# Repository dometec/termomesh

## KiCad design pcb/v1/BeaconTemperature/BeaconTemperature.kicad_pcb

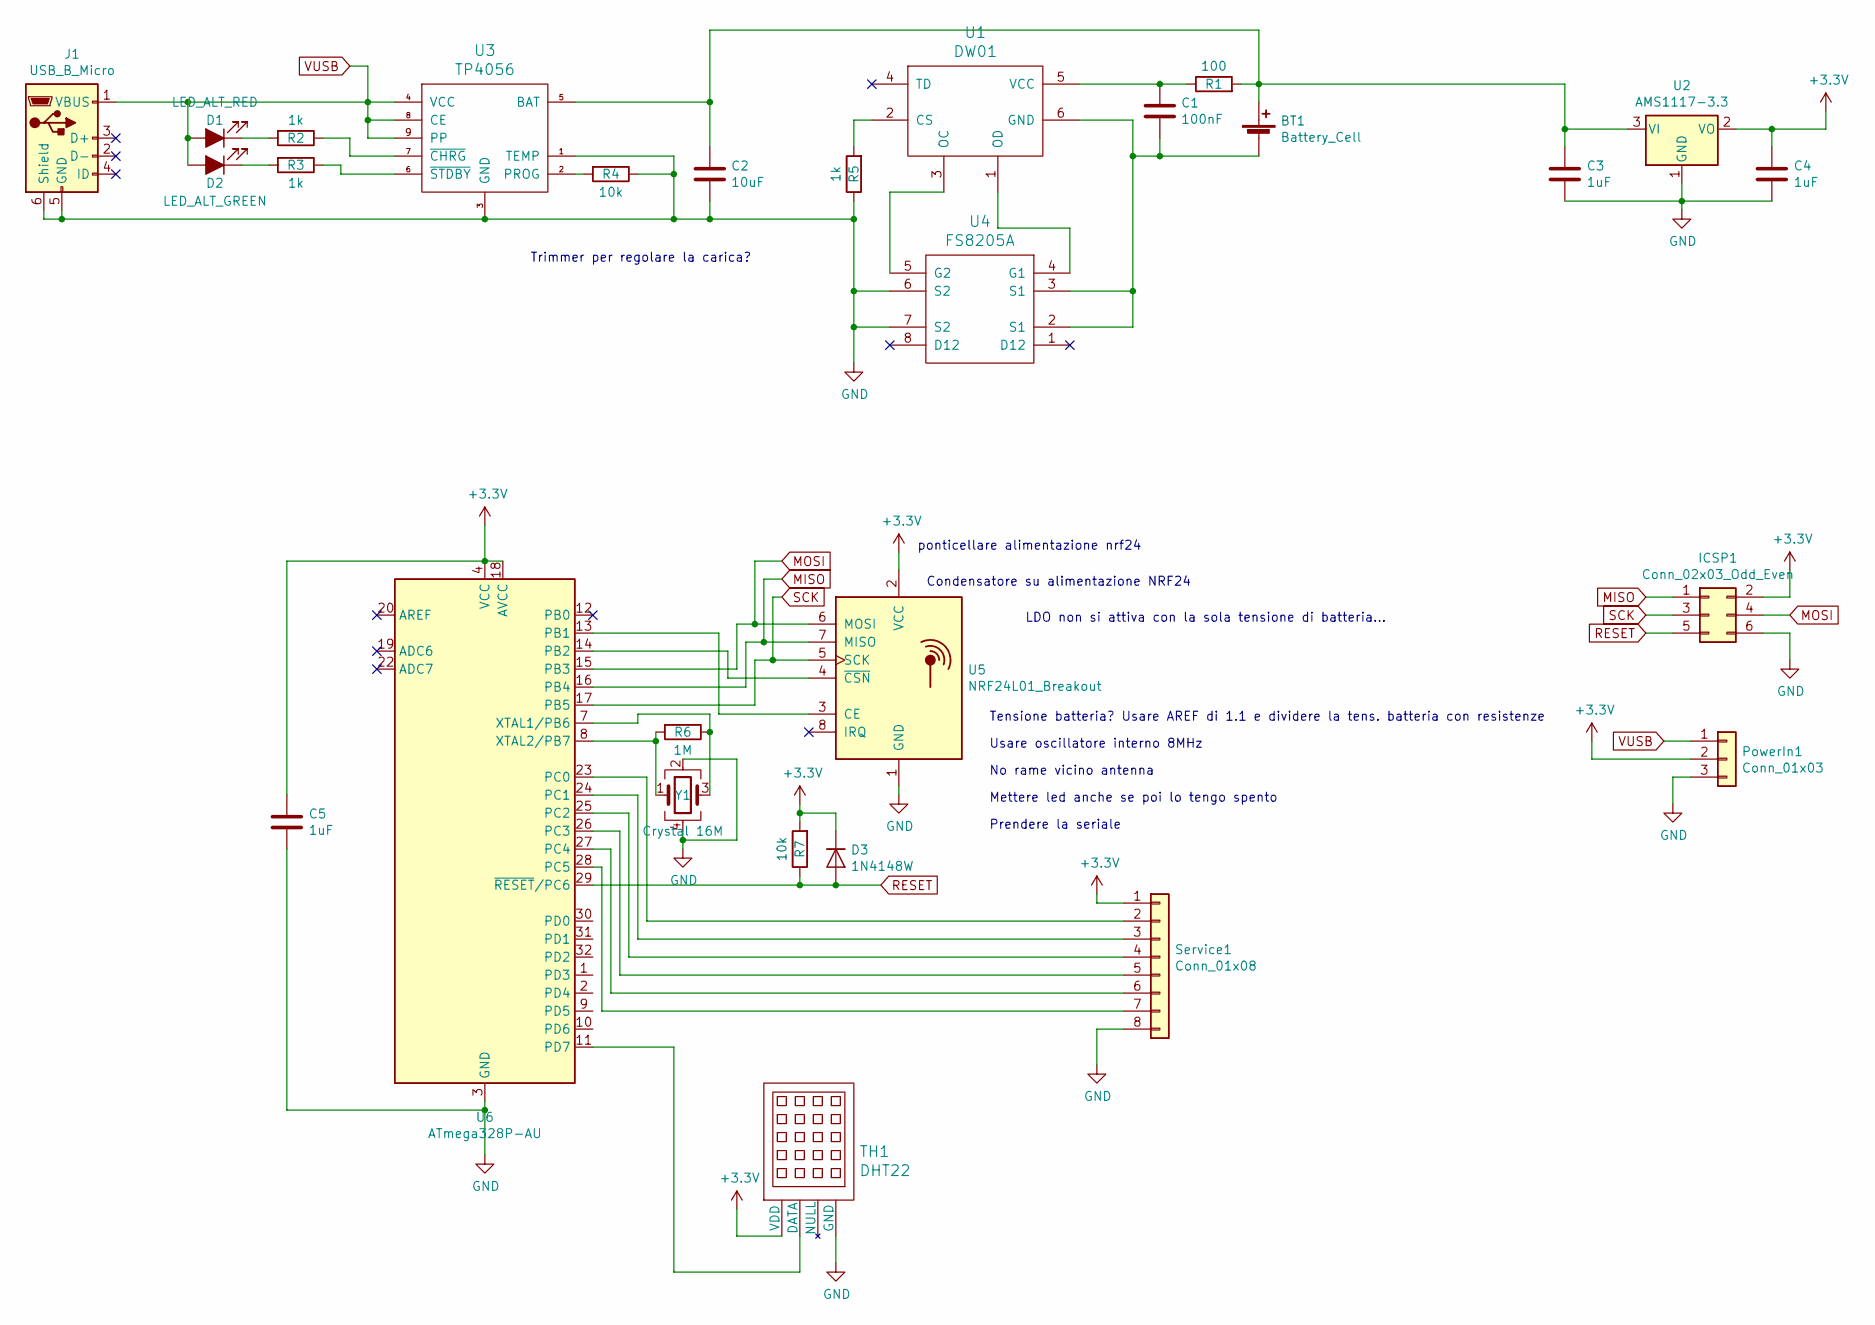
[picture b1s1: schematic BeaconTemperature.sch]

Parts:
BT1: Battery_Cell; BatteryHolder_MPD_BH-18650-PC2
C1: 100nF; C_0603_1608Metric; LCSC C14663
C2: 10uF; C_0603_1608Metric; LCSC C19702
C3, C4: 1uF; C_0603_1608Metric; LCSC C1525
C5: 1uF; C_0805_2012Metric; LCSC C28323
D1: LED_ALT_RED; LED_0603_1608Metric; LCSC C2286
D2: LED_ALT_GREEN; LED_0603_1608Metric; LCSC C72043
D3: 1N4148W; D_SOD-323F; LCSC C2128
ICSP1: Conn_02x03_Odd_Even; PinHeader_2x03_P2.54mm_Vertical
J1: USB_B_Micro; USB_Micro-B_Molex_47346-0001
PowerIn1: Conn_01x03; PinHeader_1x03_P2.54mm_Vertical
R1: 100; R_0603_1608Metric; LCSC C22775
R2, R3, R5: 1k; R_0603_1608Metric; LCSC C21190
R4, R7: 10k; R_0603_1608Metric; LCSC C25804
R6: 1M; R_0603_1608Metric; LCSC C22935
Service1: Conn_01x08; PinHeader_1x08_P2.54mm_Vertical
TH1: DHT22; DHT22_Temperature_Humidity
U1: DW01; SOT-23-6; LCSC C14213
U2: AMS1117-3.3; SOT-223-3_TabPin2; LCSC C6186
U3: TP4056; TP4056_SOP-8-PP; LCSC C16581
U4: FS8205A; TSSOP-8_4.4x3mm_P0.65mm; LCSC C16052
U5: NRF24L01_Breakout; NRF24L01-SMD
U6: ATmega328P-AU; TQFP-32_7x7mm_P0.8mm; LCSC C14877
Y1: Crystal 16M; Oscillator_SMD_EuroQuartz_XO32-4Pin_3.2x2.5mm; LCSC C13738

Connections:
+3V3: C4.1, C5.1, D3.1 (K), ICSP1.2, PowerIn1.2, R7.2, Service1.1, TH1.1 (VDD), U2.2 (VO), U5.2 (VCC), U6.4 (VCC), U6.6 (VCC), U6.18 (AVCC)
GND: C2.2, C3.2, C4.2, C5.2, ICSP1.6, J1.5 (GND), J1.6 (Shield), PowerIn1.3, R4.1, R5.1, Service1.8, TH1.4 (GND), U2.1 (GND), U3.1 (TEMP), U3.3 (GND), U4.6 (S2), U4.7 (S2), U5.1 (GND), U6.3 (GND), U6.5 (GND), U6.21 (GND), Y1.2, Y1.4
MISO: ICSP1.1, U5.7 (MISO), U6.16 (PB4)
MOSI: ICSP1.4, U5.6 (MOSI), U6.15 (PB3)
unnamed: BT1.1 (+), C2.1, C3.1, R1.2, U2.3 (VI), U3.5 (BAT)
unnamed: BT1.2 (-), C1.2, U1.6 (GND), U4.2 (S1), U4.3 (S1)
unnamed: C1.1, R1.1, U1.5 (VCC)
unnamed: D1.1 (K), R2.2
unnamed: D2.1 (K), R3.2
unnamed: R2.1, U3.7 (~CHRG)
unnamed: R3.1, U3.6 (~STDBY)
unnamed: R4.2, U3.2 (PROG)
unnamed: R5.2, U1.2 (CS)
unnamed: R6.1, U6.7 (XTAL1/PB6), Y1.3
unnamed: R6.2, U6.8 (XTAL2/PB7), Y1.1
unnamed: Service1.2, U6.23 (PC0)
unnamed: Service1.3, U6.24 (PC1)
unnamed: Service1.4, U6.25 (PC2)
unnamed: Service1.5, U6.26 (PC3)
unnamed: Service1.6, U6.27 (PC4)
unnamed: Service1.7, U6.28 (PC5)
unnamed: TH1.2 (DATA), U6.11 (PD7)
unnamed: U1.1 (OD), U4.4 (G1)
unnamed: U1.3 (OC), U4.5 (G2)
unnamed: U5.3 (CE), U6.13 (PB1)
unnamed: U5.4 (~CSN), U6.14 (PB2)
RESET: D3.2 (A), ICSP1.5, R7.1, U6.29 (~RESET~/PC6)
SCK: ICSP1.3, U5.5 (SCK), U6.17 (PB5)
VUSB: D1.2 (A), D2.2 (A), J1.1 (VBUS), PowerIn1.1, U3.4 (VCC), U3.8 (CE), U3.9 (PP)

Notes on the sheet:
Prendere la seriale
Mettere led anche se poi lo tengo spento
No rame vicino antenna
Usare oscillatore interno 8MHz
ponticellare alimentazione nrf24
Tensione batteria? Usare AREF di 1.1 e dividere la tens. batteria con resistenze
Trimmer per regolare la carica?
LDO non si attiva con la sola tensione di batteria...
Condensatore su alimentazione NRF24

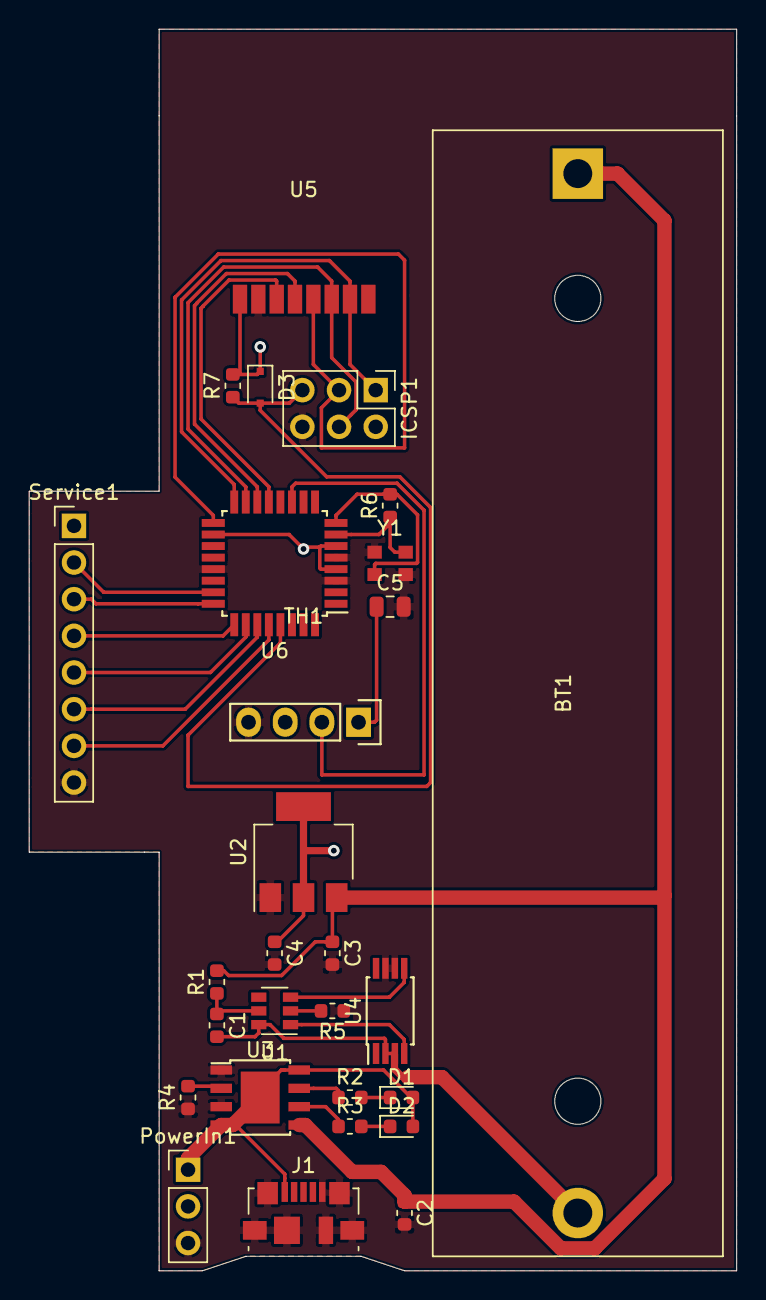
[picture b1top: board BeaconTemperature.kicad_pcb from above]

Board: 2 copper layers, 49.0 x 86.0 mm, 28 parts (0 on the bottom side), 29 nets.

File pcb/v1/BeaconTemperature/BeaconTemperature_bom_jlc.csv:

"Comment","Designator","Footprint","LCSC Part #"
"100nF","C1","C_0603_1608Metric","C14663"
"10uF","C2","C_0603_1608Metric","C19702"
"1uF","C4,C3","C_0603_1608Metric","C1525"
"1uF","C5","C_0805_2012Metric","C28323"
"LED_ALT_RED","D1","LED_0603_1608Metric","C2286"
"LED_ALT_GREEN","D2","LED_0603_1608Metric","C72043"
"1N4148W","D3","D_SOD-323F","C2128"
"100","R1","R_0603_1608Metric","C22775"
"1k","R2,R3,R5","R_0603_1608Metric","C21190"
"10k","R4,R7","R_0603_1608Metric","C25804"
"1M","R6","R_0603_1608Metric","C22935"
"DW01","U1","SOT-23-6","C14213"
"AMS1117-3.3","U2","SOT-223-3_TabPin2","C6186"
"TP4056","U3","TP4056_SOP-8-PP","C16581"
"FS8205A","U4","TSSOP-8_4.4x3mm_P0.65mm","C16052"
"ATmega328P-AU","U6","TQFP-32_7x7mm_P0.8mm","C14877"
"Crystal 16M","Y1","Oscillator_SMD_EuroQuartz_XO32-4Pin_3.2x2.5mm","C13738"

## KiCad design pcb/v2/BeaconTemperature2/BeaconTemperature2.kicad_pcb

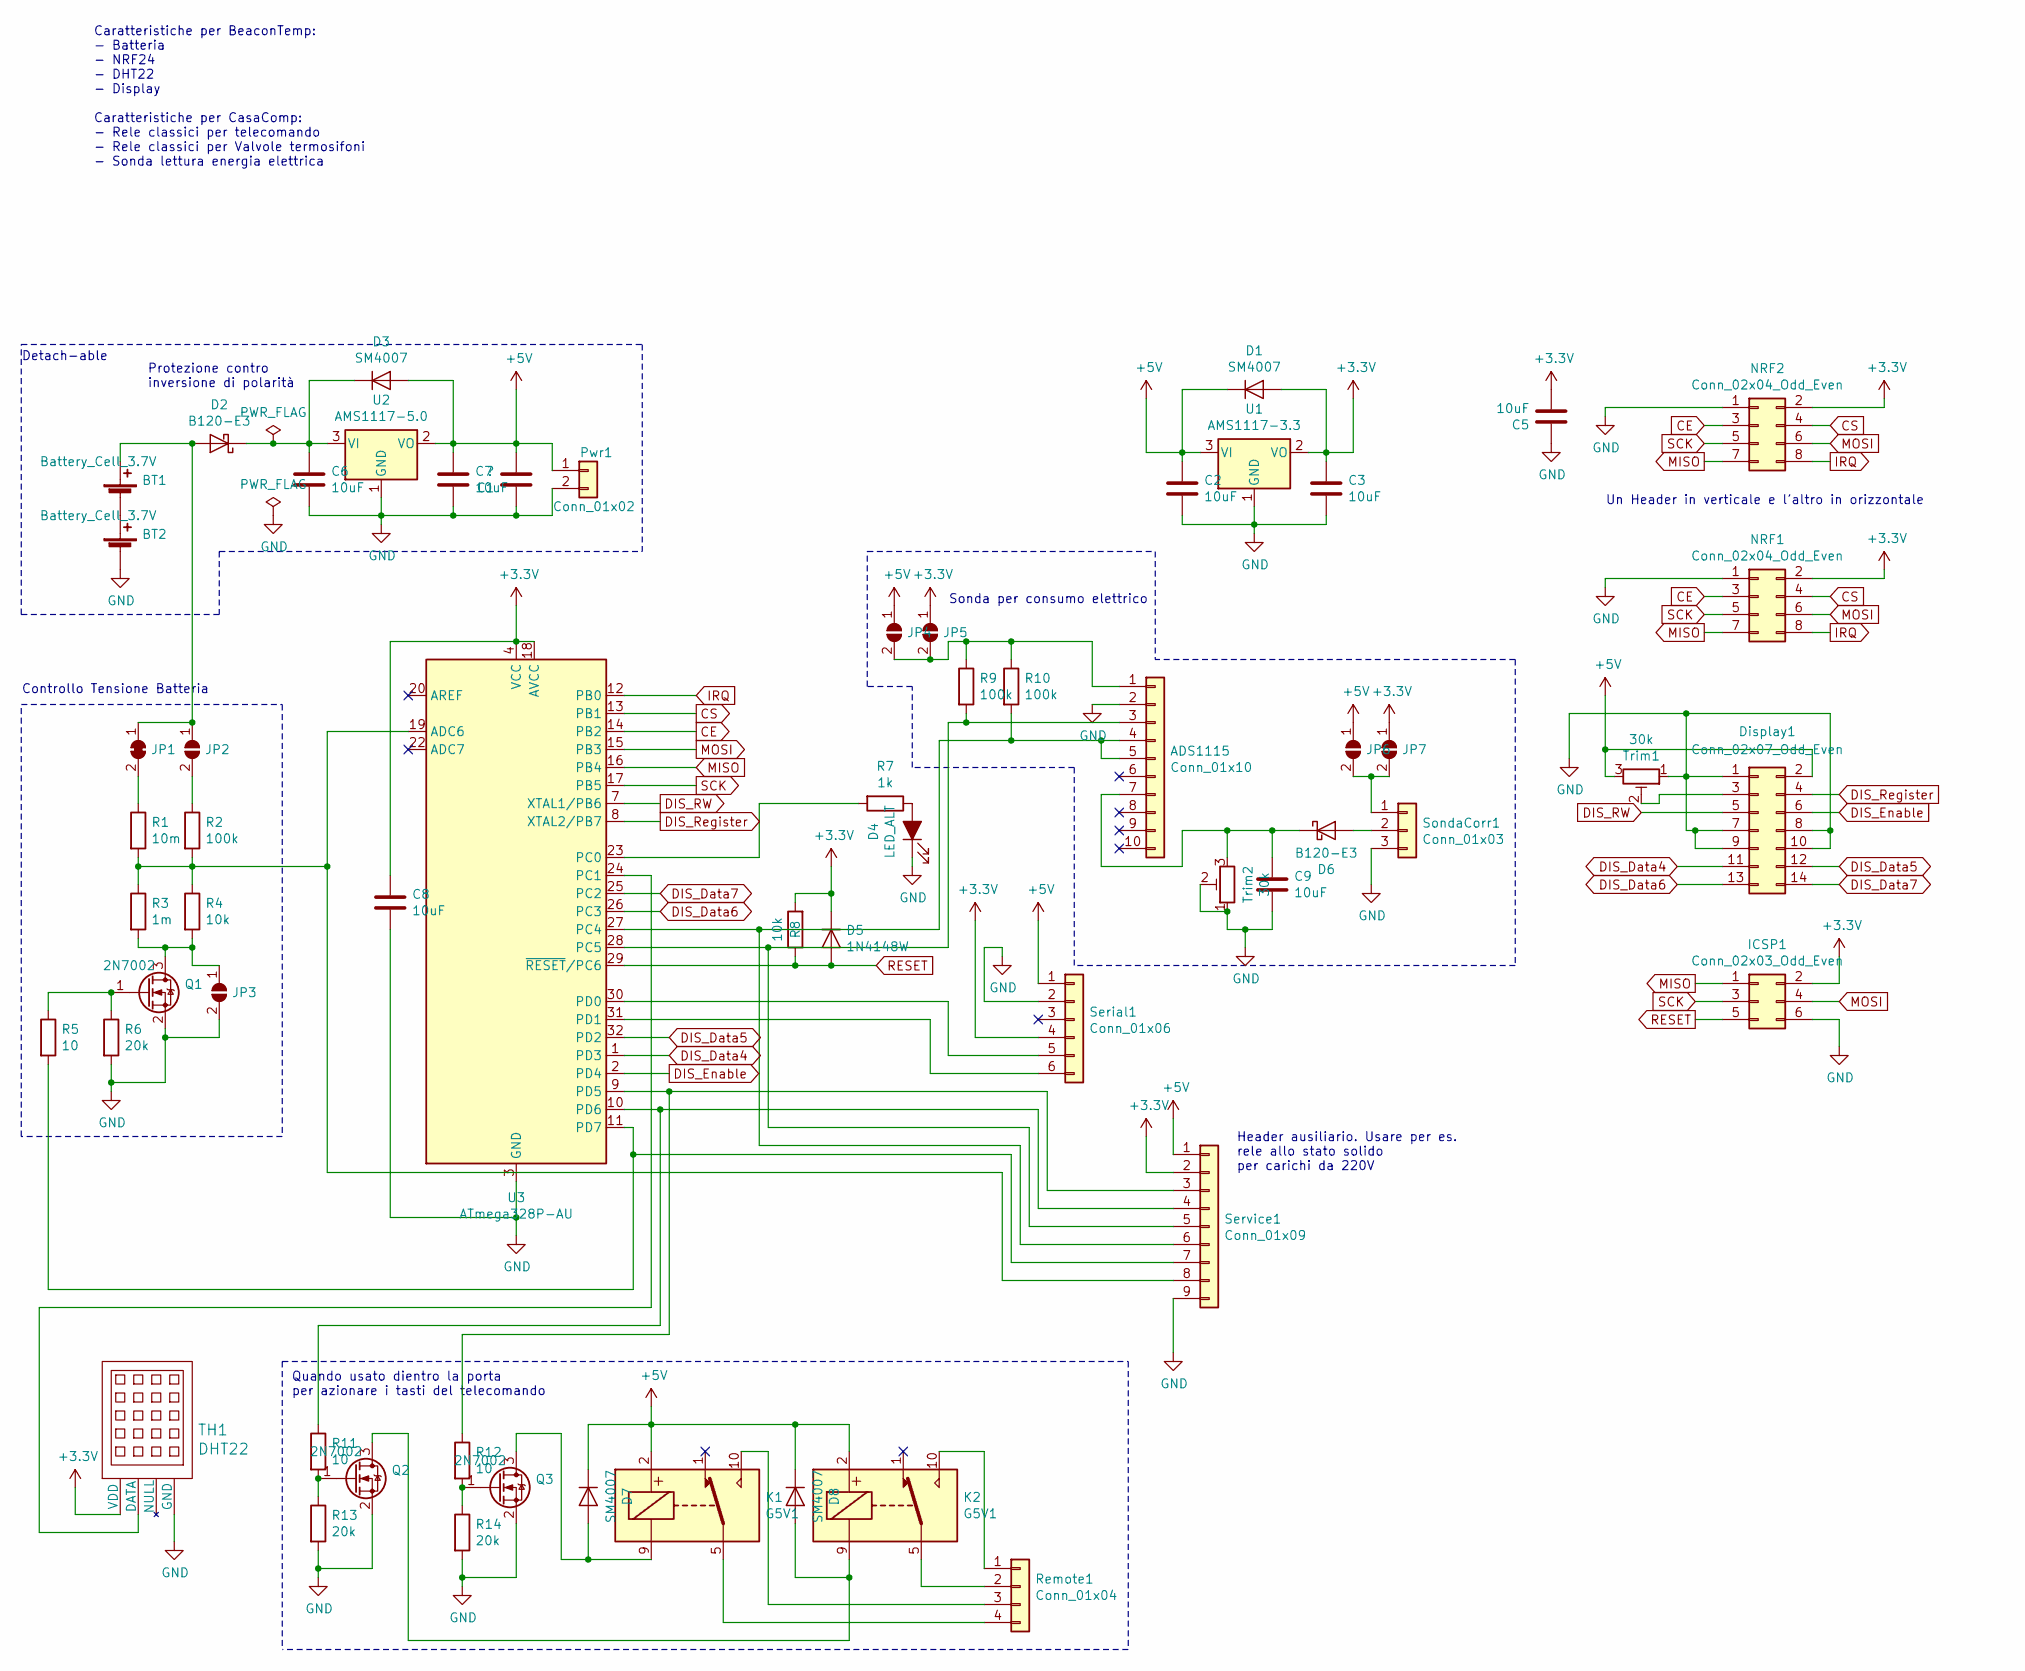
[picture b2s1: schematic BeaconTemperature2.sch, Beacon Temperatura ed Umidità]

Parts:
ADS1115: Conn_01x10; PinSocket_1x10_P2.54mm_Vertical
BT1, BT2: Battery_Cell_3.7V; BatteryHolder_MPD_BH-18650-PC2
C1: ?; CP_Radial_D8.0mm_P5.00mm
C2, C3, C5, C6, C7, C8, C9: 10uF; C_0603_1608Metric; LCSC C19702
D1, D3, D7, D8: SM4007; D_SOD-123F; LCSC C64898
D2, D6: B120-E3; D_SMA; LCSC C2480
D4: LED_ALT; LED_0603_1608Metric; LCSC C72043
D5: 1N4148W; D_SOD-323F; LCSC C2128
Display1: Conn_02x07_Odd_Even; PinHeader_2x07_P2.54mm_Vertical
ICSP1: Conn_02x03_Odd_Even; PinHeader_2x03_P2.54mm_Vertical
JP1: SolderJumper_2_Closed; SolderJumper-2_P1.3mm_Bridged_RoundedPad1.0x1.5mm
JP2, JP3, JP4, JP5, JP6, JP7: SolderJumper_2_Open; SolderJumper-2_P1.3mm_Open_RoundedPad1.0x1.5mm
K1, K2: G5V1; Relay_SPDT_Omron_G5V-1
NRF1, NRF2: Conn_02x04_Odd_Even; PinSocket_2x04_P2.54mm_Vertical
Pwr1: Conn_01x02; PinHeader_1x02_P2.54mm_Vertical
Q1, Q2, Q3: 2N7002; SOT-23; LCSC C8545
R1: 10m; R_0402_1005Metric; LCSC C26082
R2, R9, R10: 100k; R_0402_1005Metric; LCSC C25741
R3: 1m; R_0402_1005Metric; LCSC C26083
R4, R8: 10k; R_0402_1005Metric; LCSC C25744
R5, R11, R12: 10; R_0402_1005Metric; LCSC C25077
R6, R13, R14: 20k; R_0402_1005Metric; LCSC C25765
R7: 1k; R_0402_1005Metric; LCSC C11702
Remote1: Conn_01x04; PinHeader_1x04_P2.54mm_Vertical
Serial1: Conn_01x06; PinHeader_1x06_P2.54mm_Vertical
Service1: Conn_01x09; PinHeader_1x09_P2.54mm_Vertical
SondaCorr1: Conn_01x03; PinHeader_1x03_P2.54mm_Vertical
TH1: DHT22; DHT22_Temperature_Humidity
Trim1, Trim2: 30k; Potentiometer_Bourns_3296W_Vertical
U1: AMS1117-3.3; SOT-223-3_TabPin2; LCSC C6186
U2: AMS1117-5.0; SOT-223-3_TabPin2; LCSC C6187
U3: ATmega328P-AU; TQFP-32_7x7mm_P0.8mm; LCSC C14877

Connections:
+3V3: C3.1, C5.2, C8.1, D1.2 (A), D5.1 (K), ICSP1.2, JP5.1 (A), JP7.1 (A), NRF1.2, NRF2.2, R8.2, Serial1.4, Service1.2, TH1.1 (VDD), U1.2 (VO), U3.4 (VCC), U3.6 (VCC), U3.18 (AVCC)
+5V: C1.2, C2.1, C7.1, D1.1 (K), D3.2 (A), D7.1 (K), D8.1 (K), Display1.2, JP4.1 (A), JP6.1 (A), K1.2, K2.2, Pwr1.1, Serial1.1, Service1.1, Trim1.3, U1.3 (VI), U2.2 (VO)
CE: NRF1.3, NRF2.3, U3.14 (PB2)
CS: NRF1.4, NRF2.4, U3.13 (PB1)
DIS_Data4: Display1.11, U3.1 (PD3)
DIS_Data5: Display1.12, U3.32 (PD2)
DIS_Data6: Display1.13, U3.26 (PC3)
DIS_Data7: Display1.14, U3.25 (PC2)
DIS_Enable: Display1.6, U3.2 (PD4)
DIS_RW: Display1.5, U3.7 (XTAL1/PB6)
DIS_Register: Display1.4, U3.8 (XTAL2/PB7)
GND: ADS1115.2, BT2.2 (-), C1.1, C2.2, C3.2, C5.1, C6.2, C7.2, C8.2, C9.2, D4.1 (K), Display1.1, Display1.7, Display1.8, Display1.9, Display1.10, ICSP1.6, JP3.2 (B), NRF1.1, NRF2.1, Pwr1.2, Q1.2 (S), Q2.2 (S), Q3.2 (S), R6.2, R13.2, R14.2, Serial1.2, Service1.9, SondaCorr1.3, TH1.4 (GND), Trim1.1, Trim2.1, Trim2.2, U1.1 (GND), U2.1 (GND), U3.3 (GND), U3.5 (GND), U3.21 (GND)
IRQ: NRF1.8, NRF2.8, U3.12 (PB0)
MISO: ICSP1.1, NRF1.7, NRF2.7, U3.16 (PB4)
MOSI: ICSP1.4, NRF1.6, NRF2.6, U3.15 (PB3)
unnamed: ADS1115.1, JP4.2 (B), JP5.2 (B), R9.1, R10.1
unnamed: ADS1115.3, R9.2, Service1.5, U3.28 (PC5)
unnamed: ADS1115.4, ADS1115.5, R10.2, Service1.6, U3.27 (PC4)
unnamed: ADS1115.7, C9.1, D6.1 (K), Trim2.3
unnamed: BT1.1 (+), D2.2 (A), JP1.1 (A), JP2.1 (A)
unnamed: BT1.2 (-), BT2.1 (+)
unnamed: C6.1, D2.1 (K), D3.1 (K), U2.3 (VI)
unnamed: D4.2 (A), R7.1
unnamed: D6.2 (A), SondaCorr1.2
unnamed: D7.2 (A), K1.9, Q3.3 (D)
unnamed: D8.2 (A), K2.9, Q2.3 (D)
unnamed: Display1.3, Trim1.2
unnamed: JP1.2 (B), R1.1
unnamed: JP2.2 (B), R2.1
unnamed: JP3.1 (A), Q1.3 (D), R3.2, R4.2
unnamed: JP6.2 (B), JP7.2 (B), SondaCorr1.1
unnamed: K1.5, K1.6, Remote1.4
unnamed: K1.10, Remote1.3
unnamed: K2.5, K2.6, Remote1.2
unnamed: K2.10, Remote1.1
unnamed: Q1.1 (G), R5.1, R6.1
unnamed: Q2.1 (G), R11.2, R13.1
unnamed: Q3.1 (G), R12.2, R14.1
unnamed: R1.2, R2.2, R3.1, R4.1, Service1.8, U3.19 (ADC6)
unnamed: R5.2, Service1.7, U3.11 (PD7)
unnamed: R7.2, U3.23 (PC0)
unnamed: R11.1, Service1.4, U3.10 (PD6)
unnamed: R12.1, Service1.3, U3.9 (PD5)
unnamed: Serial1.5, U3.30 (PD0)
unnamed: Serial1.6, U3.31 (PD1)
unnamed: TH1.2 (DATA), U3.24 (PC1)
RESET: D5.2 (A), ICSP1.5, R8.1, U3.29 (~RESET~/PC6)
SCK: ICSP1.3, NRF1.5, NRF2.5, U3.17 (PB5)

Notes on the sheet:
Controllo Tensione Batteria
Protezione contro inversione di polarità
Quando usato dientro la porta per azionare i tasti del telecomando
Header ausiliario. Usare per es. rele allo stato solido per carichi da 220V
Sonda per consumo elettrico
Caratteristiche per BeaconTemp: - Batteria - NRF24 - DHT22 - Display Caratteristiche per CasaComp: - Rele classici per telecomando - Rele classici per Valvole termosifoni - Sonda lettura energia elettrica
Un Header in verticale e l'altro in orizzontale
Detach-able

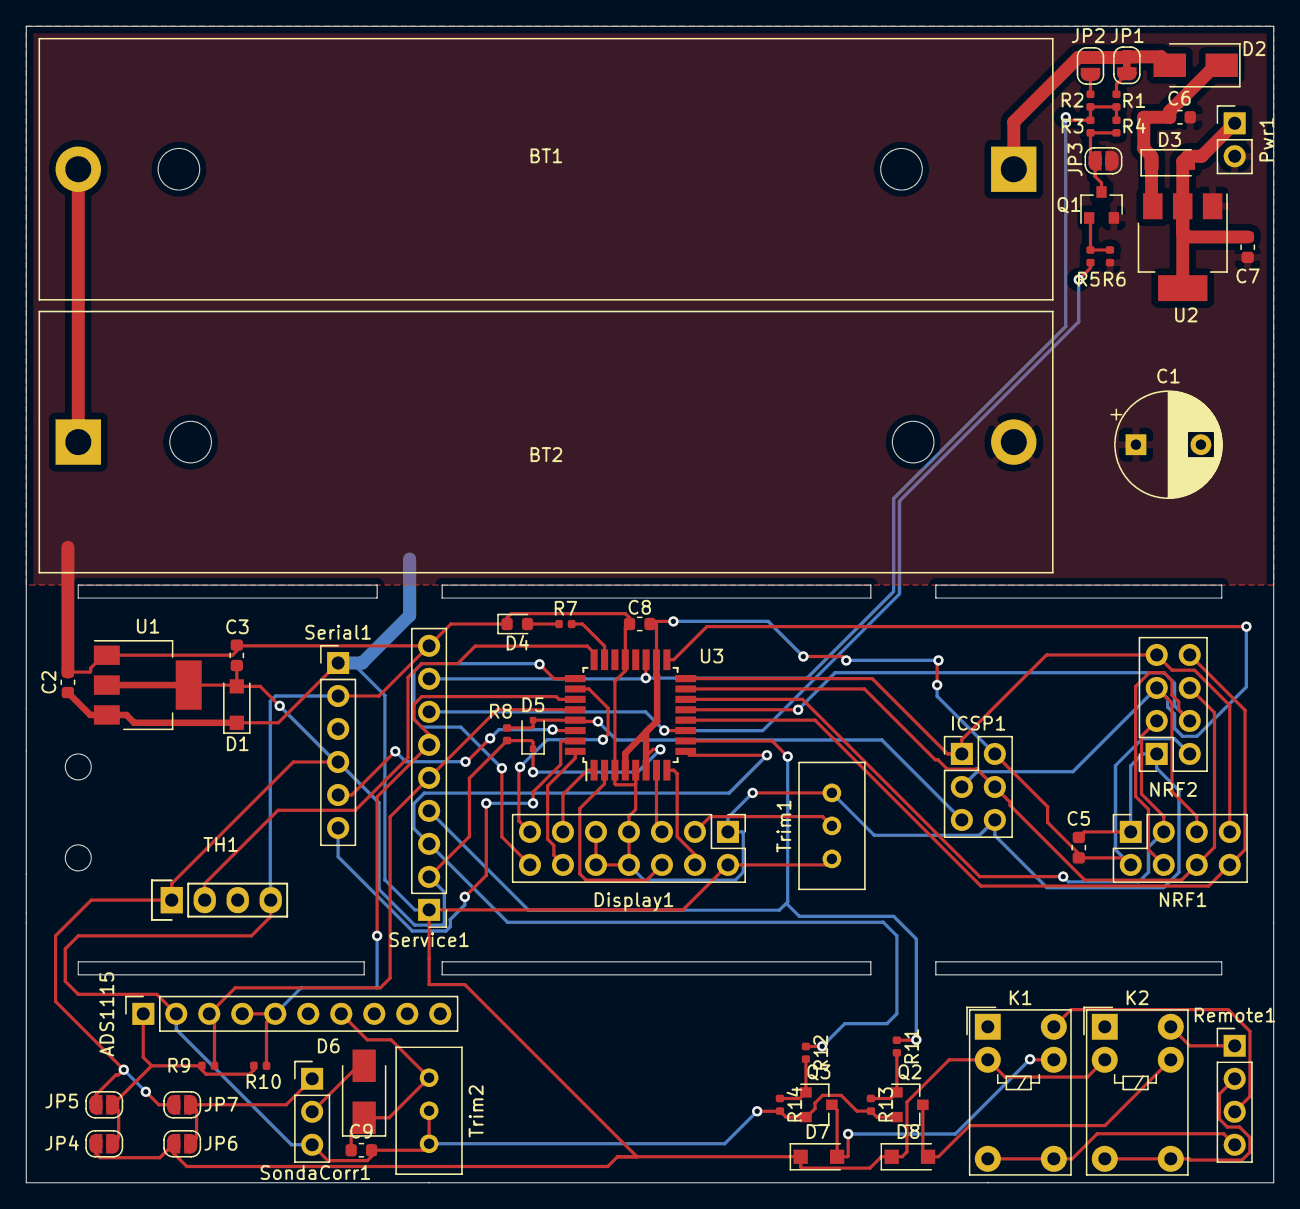
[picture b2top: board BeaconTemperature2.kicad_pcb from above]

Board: 2 copper layers, 96.0 x 89.0 mm, 60 parts (0 on the bottom side), 48 nets.

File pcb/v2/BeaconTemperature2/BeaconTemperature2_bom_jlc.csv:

"Comment","Designator","Footprint","LCSC Part #"
"10uF","C2,C3,C8,C5,C6,C7,C9","C_0603_1608Metric","C19702"
"SM4007","D1,D3,D8,D7","D_SOD-123F","C64898"
"B120-E3","D2,D6","D_SMA","C2480"
"LED_ALT","D4","LED_0603_1608Metric","C72043"
"1N4148W","D5","D_SOD-323F","C2128"
"2N7002","Q1,Q2,Q3","SOT-23","C8545"
"10m","R1","R_0402_1005Metric","C26082"
"100k","R2,R9,R10","R_0402_1005Metric","C25741"
"1m","R3","R_0402_1005Metric","C26083"
"10","R5,R11,R12","R_0402_1005Metric","C25077"
"20k","R6,R13,R14","R_0402_1005Metric","C25765"
"1k","R7","R_0402_1005Metric","C11702"
"10k","R8,R4","R_0402_1005Metric","C25744"
"AMS1117-3.3","U1","SOT-223-3_TabPin2","C6186"
"AMS1117-5.0","U2","SOT-223-3_TabPin2","C6187"
"ATmega328P-AU","U3","TQFP-32_7x7mm_P0.8mm","C14877"
